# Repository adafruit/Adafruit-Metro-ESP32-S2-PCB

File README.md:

## Adafruit Metro ESP32-S2 PCB

<a href="http://www.adafruit.com/products/4775"><br/>
Click here to purchase one from the Adafruit shop</a>

PCB files for the Adafruit Metro ESP32-S2.

Format is EagleCAD schematic and board layout
* https://www.adafruit.com/product/4775

### Description

What's Metro shaped and has an ESP32-S2 WiFi module? What has a STEMMA QT connector for I2C devices, and a Lipoly charger circuit? What's finishing up testing and nearly ready for fabrication? That's right - its the new Adafruit Metro ESP32-S2! With native USB and a load of PSRAM this board is perfect for use with CircuitPython or Arduino, to add low-cost WiFi while keeping shield-compatibility

Features:

* ESP32-S2 240MHz Tensilica processor - the next generation of ESP32, now with native USB so it can act like a keyboard/mouse, MIDI device, disk drive, etc!
* WROVER module has FCC/CE certification and comes with 4 MByte of Flash and 8 MByte of PSRAM - you can have huge data buffers
* Lotsa power options - 6-12VDC barrel jack or USB type C or Lipoly battery
* Built-in battery charging when powered over DC or USB
* UNO-shape so shields can plug in
* Reset and DFU (BOOT0) buttons to get into the ROM bootloader (which is a USB serial port so you don't need a separate cable!)
* Serial debug pins (optional, for checking the hardware serial debug console)
* JTAG pads for advanced debugging access.
* On/Off switch
* STEMMA QT connector for I2C devices
* On/Charge/User LEDs + status NeoPixel
* Works with Arduino or CircuitPython
* 53.2mm x 72mm / 2" x 2.8"
* Height (w/ barrel jack): 14.8mm / 0.6"
* Weight: 22.5g

### License

Adafruit invests time and resources providing this open source design, please support Adafruit and open-source hardware by purchasing products from [Adafruit](https://www.adafruit.com)!

Designed by Limor Fried/Ladyada for Adafruit Industries.

Creative Commons Attribution/Share-Alike, all text above must be included in any redistribution.
See license.txt for additional details.

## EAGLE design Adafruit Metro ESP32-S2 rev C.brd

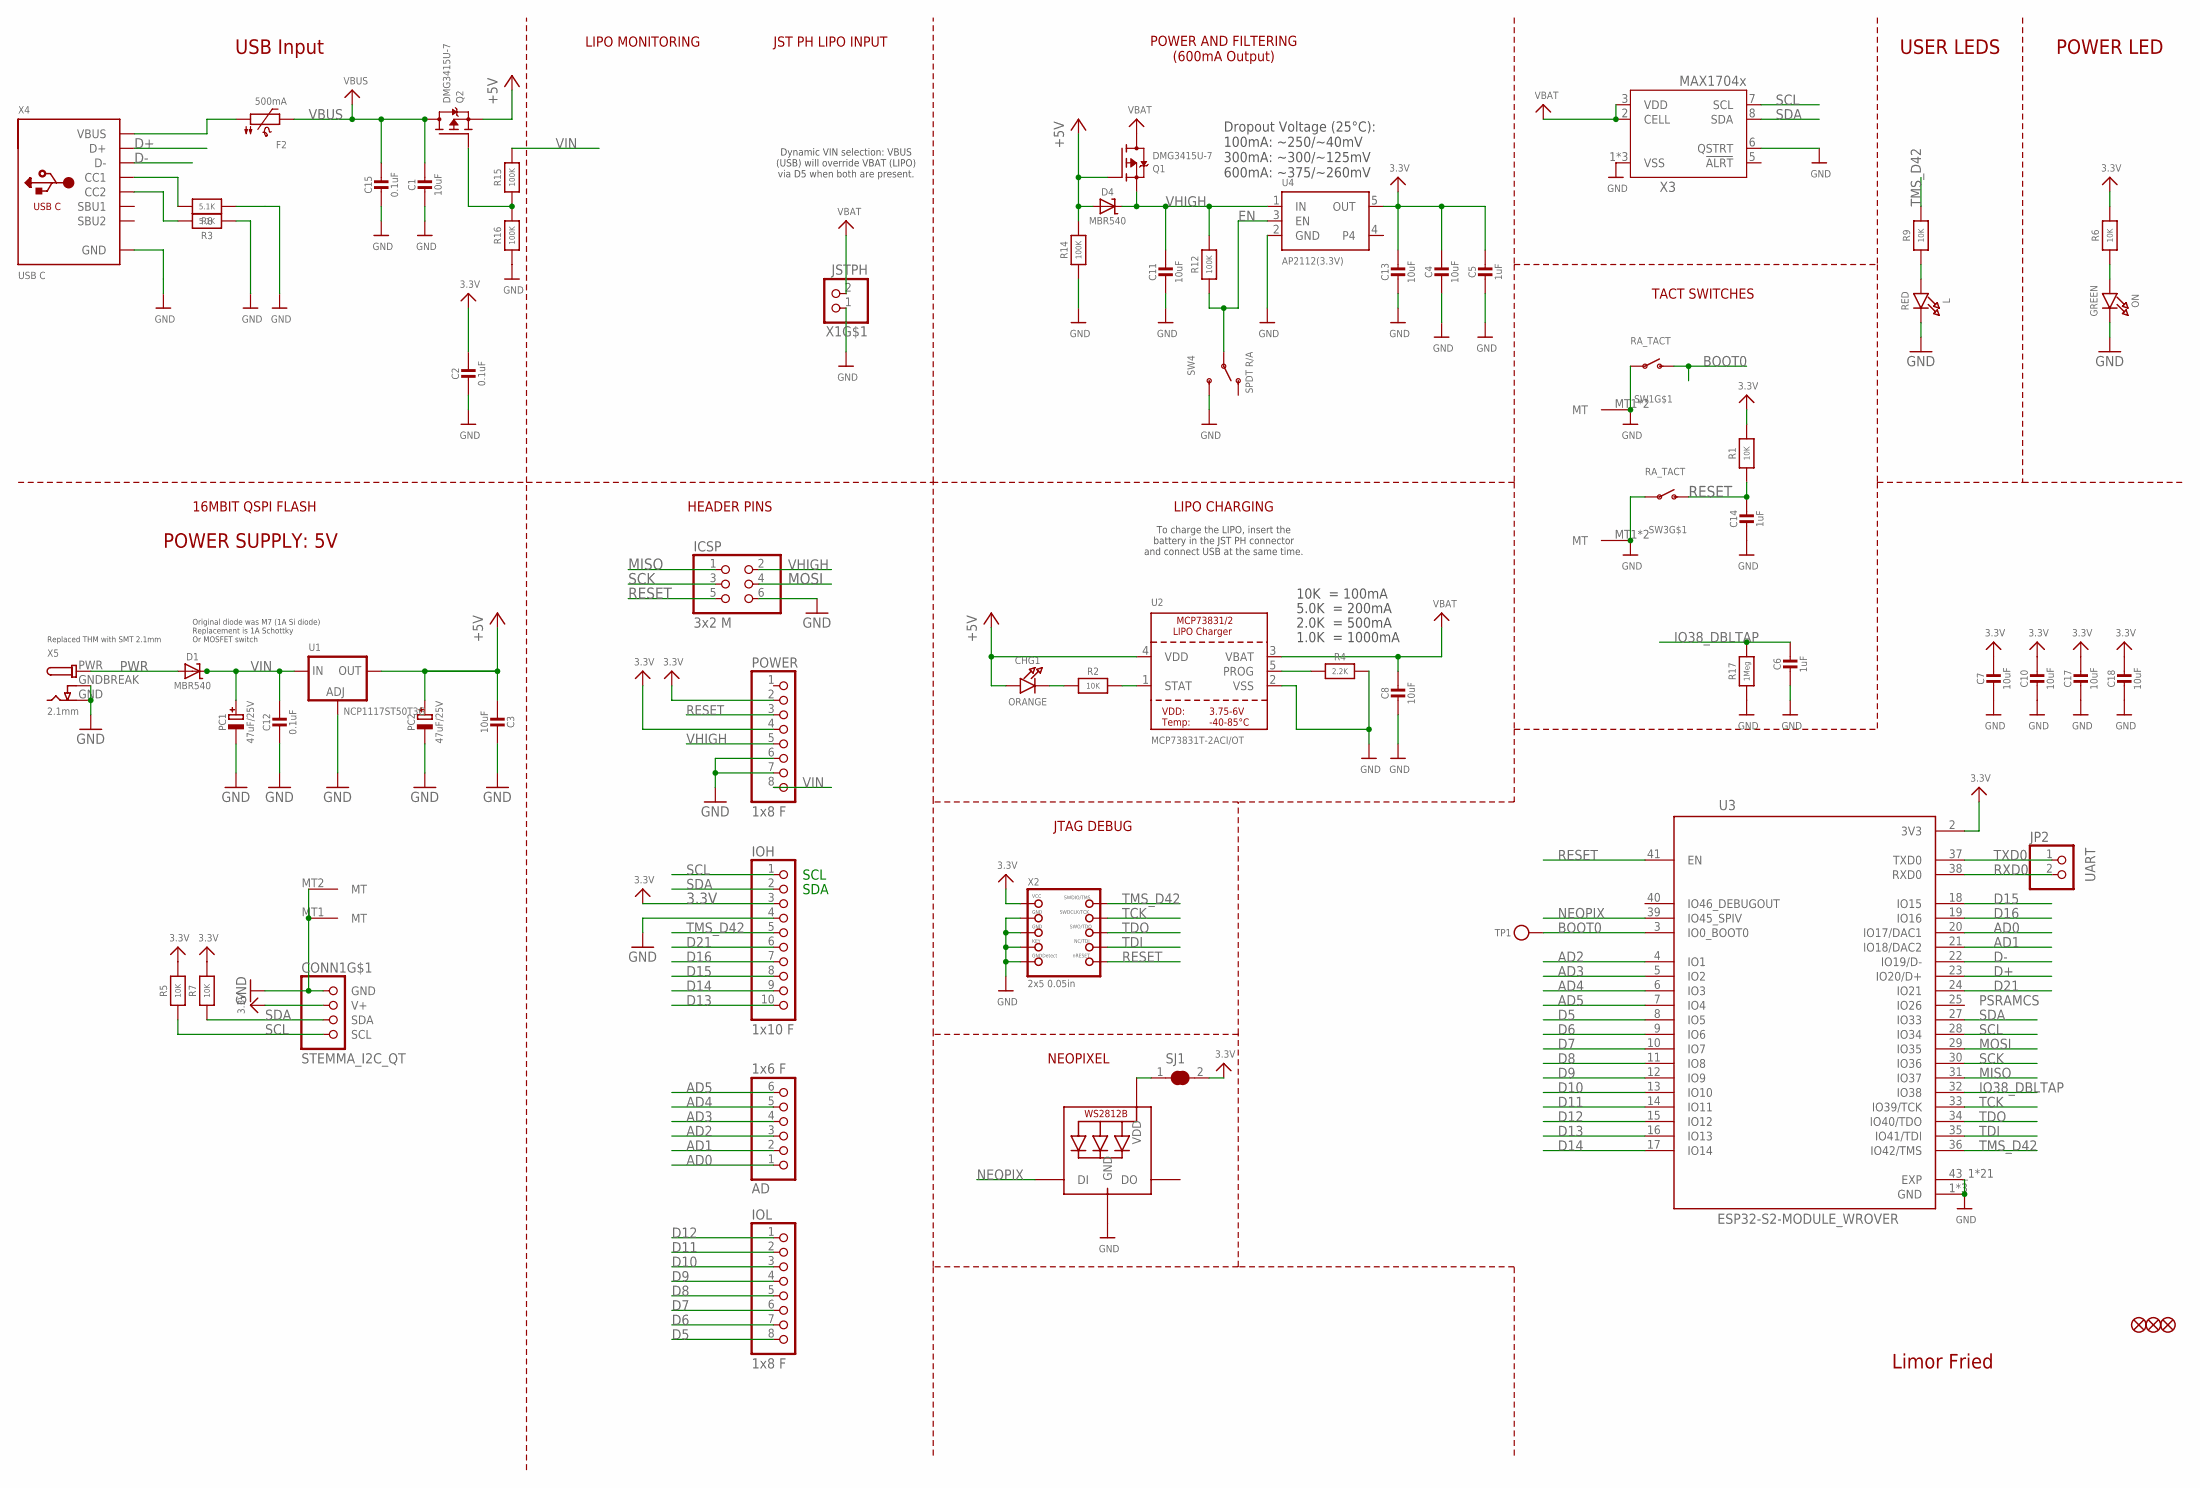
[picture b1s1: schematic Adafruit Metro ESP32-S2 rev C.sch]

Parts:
AD: 1x6 F; 1X06_OVALWAVE
C1, C3, C4, C7, C8, C10, C11, C13, C17, C18: 10uF; 0805-NO
C2, C12, C15: 0.1uF; 0603-NO
C5, C6, C14: 1uF; 0603-NO
CHG1: ORANGE; CHIPLED_0603_NOOUTLINE
CONN1: STEMMA_I2C_QT; JST_SH4
D1, D4: MBR540; SOD-123
F2: 500mA; 1206
FD1, FD2, FD3: FIDUCIAL_1MM
ICSP: 3x2 M; 2X03_ROUND_70MIL
IOH: 1x10 F; 1X10_OVALWAVE
IOL: 1x8 F; 1X08_OVALWAVE
JP2: UART; 1X02_ROUND
L: RED; CHIPLED_0603_NOOUTLINE
LED1: WS2812B_3535FULL; LED3535_FULLPADS
ON: GREEN; CHIPLED_0603_NOOUTLINE
PC1, PC2: 47uF/25V; PANASONIC_D
POWER: 1x8 F; 1X08_OVALWAVE
Q1, Q2: DMG3415U-7; SOT23-R
R1, R2, R5, R6, R7, R9: 10K; 0603-NO
R3, R8: 5.1K; 0603-NO
R4: 2.2K; 0603-NO
R12, R14, R15, R16: 100K; 0603-NO
R17: 1Meg; 0603-NO
SJ1: SOLDERJUMPER_CLOSED; SOLDERJUMPER_CLOSEDWIRE
SW1, SW3: RA_TACT; SPST_TACTILE_RA
SW4: SPDT R/A; SPDT_SMT_SSSS811101
TP1: TESTPOINTROUND1.5MMNO; TESTPOINT_ROUND_1.5MM_NO
U1: NCP1117ST50T3G; SOT223-R
U2: MCP73831T-2ACI/OT; SOT23-5
U3: ESP32-S2-MODULE_WROVER; MODULE_ESP32-S2-WROVER
U4: AP2112(3.3V); SOT23-5; JLC_ROTATION 0
X1: JSTPH; JSTPH2_BATT
X2: 2x5 0.05in; 2X05_1.27MM_BOX_POSTS
X3: MAX17048/T; TDFN8_2X2MM
X4: USB C; USB_C_CUSB31-CFM2AX-01-X
X5: 2.1mm; DCJACK_2MM_PTH

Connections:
3.3V: C2.1, C4.1, C5.1, C7.1, C10.1, C13.1, C17.1, C18.1, CONN1.2 (V+), IOH.3, POWER.2, POWER.4, R1.2, R5.2, R6.2, R7.2, SJ1.2, U3.2 (3V3), U4.5 (OUT), X2.1 (VCC)
+5V: C3.2, CHG1.A, D4.A, PC2.+, Q1.1 (G), Q2.2 (S), R14.2, U1.2 (OUT), U1.4 (OUT), U2.4 (VDD)
AD0: AD.1, U3.20 (IO17/DAC1)
AD1: AD.2, U3.21 (IO18/DAC2)
AD2: AD.3, U3.4 (IO1)
AD3: AD.4, U3.5 (IO2)
AD4: AD.5, U3.6 (IO3)
AD5: AD.6, U3.7 (IO4)
BOOT0: SW1.2 (S), TP1.P$1, U3.3 (IO0_BOOT0)
D5: IOL.8, U3.8 (IO5)
D6: IOL.7, U3.9 (IO6)
D7: IOL.6, U3.10 (IO7)
D8: IOL.5, U3.11 (IO8)
D9: IOL.4, U3.12 (IO9)
D10: IOL.3, U3.13 (IO10)
D11: IOL.2, U3.14 (IO11)
D12: IOL.1, U3.15 (IO12)
D13: IOH.10, U3.16 (IO13)
D14: IOH.9, U3.17 (IO14)
D15: IOH.8, U3.18 (IO15)
D16: IOH.7, U3.19 (IO16)
D21: IOH.6, U3.24 (IO21)
D+: U3.23 (IO20/D+), X4.A6 (D+), X4.B6 (D+)
D-: U3.22 (IO19/D-), X4.A7 (D-), X4.B7 (D-)
EN: R12.1, SW4.B, U4.3 (EN)
GND: C1.2, C2.2, C3.1, C4.2, C5.2, C6.2, C7.2, C8.2, C10.2, C11.2, C12.2, C13.2, C14.2, C15.2, C17.2, C18.2, CONN1.1 (GND), CONN1.MT1 (MT), CONN1.MT2 (MT), ICSP.6, IOH.4, L.C, LED1.4 (GND), ON.C, PC1.-, PC2.-, POWER.6, POWER.7, R3.1, R4.2, R8.1, R14.1, R16.1, R17.1, SW1.1, SW1.MT1 (MT), SW1.MT2 (MT), SW3.1, SW3.MT1 (MT), SW3.MT2 (MT), SW4.C (S), U1.1 (ADJ), U2.2 (VSS), U3.1 (GND), U3.26 (GND), U3.42 (GND), U3.43_1 (EXP), U3.43_2 (EXP), U3.43_3 (EXP), U3.43_4 (EXP), U3.43_5 (EXP), U3.43_6 (EXP), U3.43_7 (EXP), U3.43_8 (EXP), U3.43_9 (EXP), U3.43_10 (EXP), U3.43_11 (EXP), U3.43_12 (EXP), U3.43_13 (EXP), U3.43_14 (EXP), U3.43_15 (EXP), U3.43_16 (EXP), U3.43_17 (EXP), U3.43_18 (EXP), U3.43_19 (EXP), U3.43_20 (EXP), U3.43_21 (EXP), U4.2 (GND), X1.1, X2.3 (GND), X2.5 (GND), X2.7 (KEY), X2.9 (GNDDETECT), X3.1 (VSS), X3.4 (VSS), X3.6 (QSTRT), X3.THERMAL (VSS), X4.A1B12 (GND), X4.B1A12 (GND), X5.GND, X5.GNDBREAK
IO38_DBLTAP: C6.1, R17.2, U3.32 (IO38)
MISO: ICSP.1, U3.31 (IO37)
MOSI: ICSP.4, U3.29 (IO35)
unnamed: L.A, R9.1
unnamed: Q2.1 (G), R15.1, R16.2
unnamed: ON.A, R6.1
unnamed: CHG1.C, R2.1
unnamed: LED1.2 (VDD), SJ1.1
unnamed: R2.2, U2.1 (STAT)
unnamed: R8.2, X4.A5 (CC1)
unnamed: R3.2, X4.B5 (CC2)
unnamed: R4.1, U2.5 (PROG)
unnamed: F2.1, X4.A4B9 (VBUS), X4.B4A9 (VBUS)
NEOPIX: LED1.1 (DI), U3.39 (IO45_SPIV)
PWR: D1.A, X5.PWR
RESET: C14.1, ICSP.5, POWER.3, R1.1, SW3.2 (S), U3.41 (EN), X2.10 (NRESET)
RXD0: JP2.2, U3.38 (RXD0)
SCK: ICSP.3, U3.30 (IO36)
SCL: CONN1.4 (SCL), IOH.1, R5.1, U3.28 (IO34), X3.7 (SCL)
SDA: CONN1.3 (SDA), IOH.2, R7.1, U3.27 (IO33), X3.8 (SDA)
TCK: U3.33 (IO39/TCK), X2.4 (SWDCLK)
TDI: U3.35 (IO41/TDI), X2.8 (TDI)
TDO: U3.34 (IO40/TDO), X2.6 (SWO)
TMS_D42: IOH.5, R9.2, U3.36 (IO42/TMS), X2.2 (SWDIO)
TXD0: JP2.1, U3.37 (TXD0)
VBAT: C8.1, Q1.3 (D), U2.3 (VBAT), X1.2, X3.2 (CELL), X3.3 (VDD)
VBUS: C1.1, C15.1, F2.2, Q2.3 (D)
VHIGH: C11.1, D4.C, ICSP.2, POWER.5, Q1.2 (S), R12.2, U4.1 (IN)
VIN: C12.1, D1.C, PC1.+, POWER.8, R15.2, U1.3 (IN)

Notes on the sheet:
SDA
SCL
Limor Fried
USB Input
POWER LED
USER LEDS
10K = 100mA
5.0K = 200mA
2.0K = 500mA
1.0K = 1000mA
LIPO CHARGING
LIPO MONITORING
To charge the LIPO, insert the battery in the JST PH connector and connect USB at the same time.
POWER AND FILTERING (600mA Output)
JST PH LIPO INPUT
Dynamic VIN selection: VBUS (USB) will override VBAT (LIPO) via D5 when both are present.
Dropout Voltage (25°C): 100mA: ~250/~40mV 300mA: ~300/~125mV 600mA: ~375/~260mV
HEADER PINS
16MBIT QSPI FLASH
TACT SWITCHES
JTAG DEBUG
NEOPIXEL
Original diode was M7 (1A Si diode) Replacement is 1A Schottky Or MOSFET switch
Replaced THM with SMT 2.1mm
POWER SUPPLY: 5V
PSRAMCS

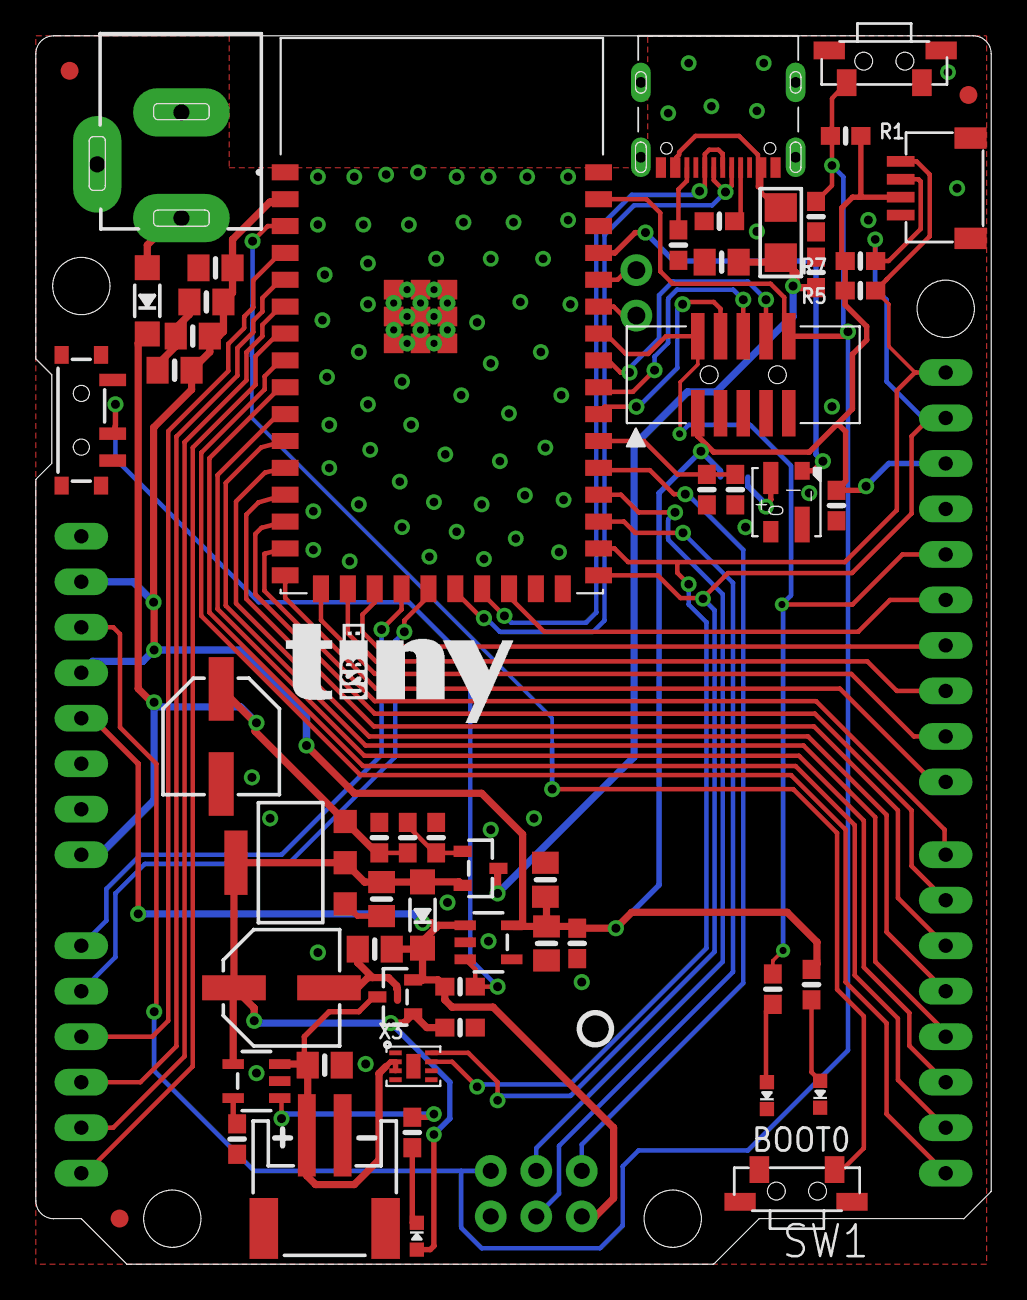
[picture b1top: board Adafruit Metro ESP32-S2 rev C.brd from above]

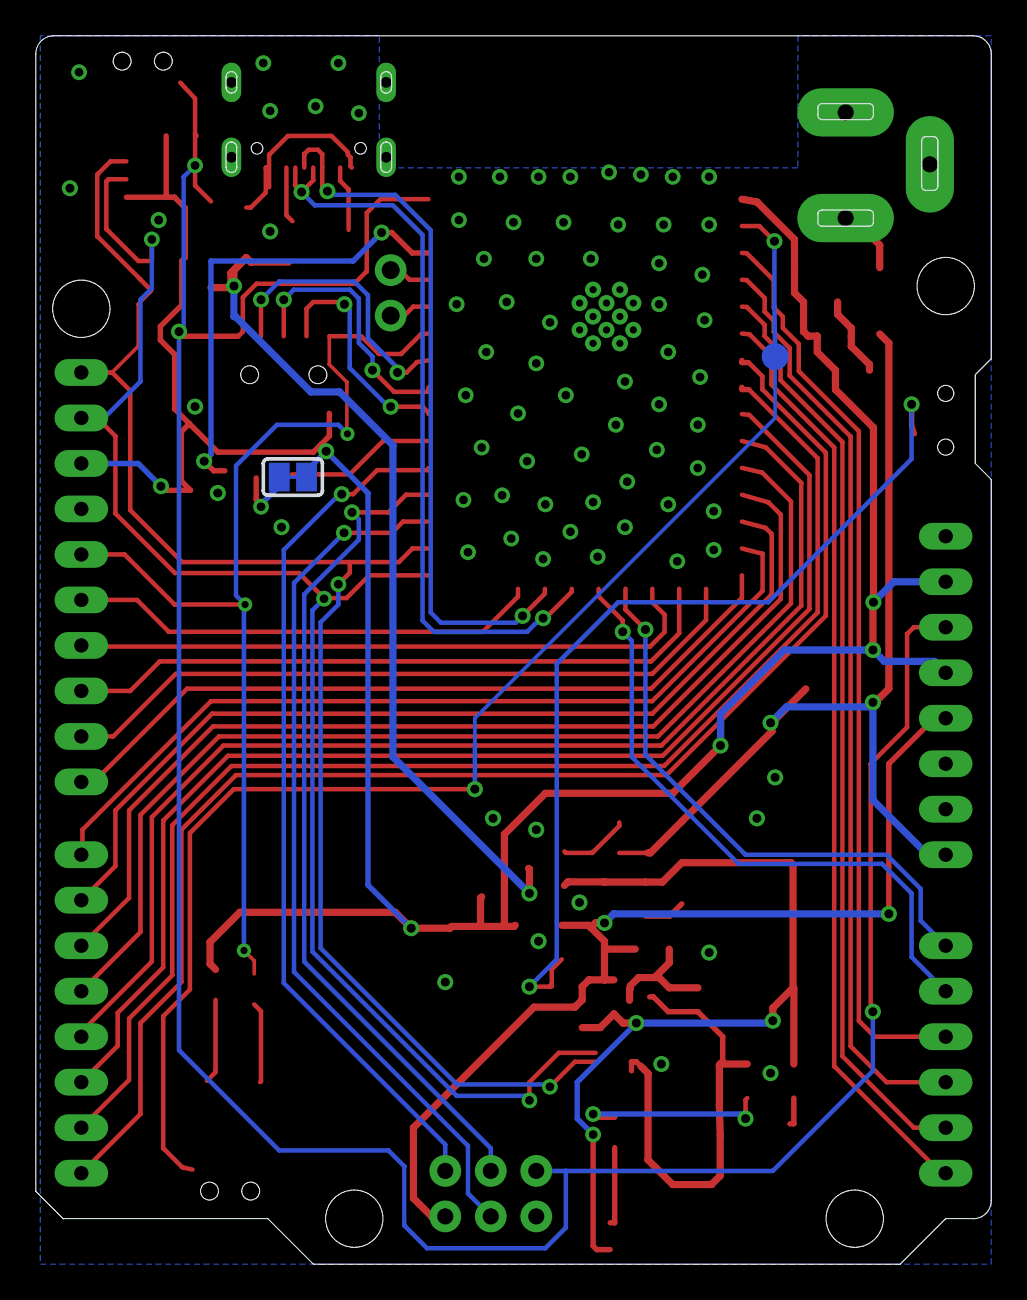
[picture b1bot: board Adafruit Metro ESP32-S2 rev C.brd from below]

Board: 2 copper layers, 53.3 x 68.6 mm, 69 parts (3 on the bottom side), 55 nets.

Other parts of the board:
U$14: TINYUSB_0.5IN
U$15: PCBFEAT-REV-040
U$52: ESP32S2_TOP
U$53: ESP32S2_BOT

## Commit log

2020-11-02 Adding board files.
2021-05-12 Add pinout reference PDF
2024-11-19 adding factory reset
2026-03-25 add rev c
2026-03-25 update image

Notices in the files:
parts and their libraries:
microbuilder: This work is placed in the public domain, and may be freely used for commercial and non-commercial work with the following conditions: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
